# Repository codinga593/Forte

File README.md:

FORTE is a mid powered rocket with an estimated flight alitude of 137m initially, and a planned 1000m flight on a high powered motor later. 
It features a miniature onboard flight computer to verify data logging and live telemetry capabilties. 
The Flight computer has an inertial measurement unit and barometer to sense it's height and orientation. A LoRa Chip is placed onboard to stream data over 915 mHz to a ground station. 

The PCB is mainly for telemetry and datalogging, running custom firmware to achieve this. To get the PCB, you can send the gerber files to your manufacturer of choice, and buy components from online services such as LCSC, digikey or mouser. The rocket kit is available from LOC Precision and costs about $90.

This Rocket is my next step in my rocketry journey, allowing me to explore telemetry onboard rockets, efficient datalogging and building up to something more complex such as active control.

Render of Final PCB

Model of Rocket

Avionics Bay CAD

## Bill of Materials (BOM)

| Designator | Part Name | Qty | Value / Part Number | Link |
|---|---|---|---|---|
| C14, C15, C16, C17, C18, C27, C28, C29, C30, C31, C35, C36 | Capacitor | 12 | 100 nF 0603 | https://www.digikey.com/en/products/detail/murata-electronics/GRM188R71C104KA01D |
| C13, C20, C21 | Capacitor | 3 | 1 µF 0603 | https://www.digikey.com/en/products/detail/murata-electronics/GRM188R61A105KA61D |
| C24, C25 | Capacitor | 2 | 2.2 µF 0603 | https://www.digikey.com/en/products/detail/murata-electronics/GRM188R61A225KE15 |
| C22, C23 | Capacitor | 2 | 10 pF 0603 | https://www.digikey.com/en/products/detail/murata-electronics/GRM1885C1H100JA01D |
| C34 | Capacitor | 1 | 22 µF 0603 | https://www.digikey.com/en/products/detail/murata-electronics/GRM188R60J226MEA0 |
| C26, C38, C39 | Capacitor | 3 | 100 nF 0603 | https://www.digikey.com/en/products/detail/murata-electronics/GRM188R71C104KA01D |
| R2, R3, R4, R8, R9, R10, R11, R12, R13, R14, R15, R18 | Resistor | 12 | 10 kΩ 0603 | https://www.digikey.com/en/products/detail/yageo/RC0603FR-0710KL |
| R16, R17 | Resistor | 2 | 0603 220Ω | https://www.digikey.com/en/products/detail/yageo/RC0603FR |
| U3 | Microcontroller | 1 | STM32F405RGT6 | https://www.digikey.com/en/products/detail/stmicroelectronics/STM32F405RGT6 |
| IC1 | SPI Flash Memory | 1 | W25Q128JVFIQ | https://www.digikey.com/en/products/detail/winbond-electronics/W25Q128JVFIQ |
| U2 | Barometric Pressure Sensor | 1 | MS5611-01BA | https://www.digikey.com/en/products/detail/te-connectivity/MS5611-01BA |
| U4 | GNSS Receiver | 1 | u-blox MAX-M10S | https://www.digikey.com/en/products/detail/u-blox/MAX-M10S-00B |
| U5 | USB ESD Protection | 1 | USBLC6-2SC6 | https://www.digikey.com/en/products/detail/stmicroelectronics/USBLC6-2SC6 |
| U13 | Buck Converter | 1 | TPS54525PWPR | https://www.digikey.com/en/products/detail/texas-instruments/TPS54525PWPR |
| Y2 | Crystal | 1 | 16 MHz SMD | https://www.digikey.com/en/products/detail/ecs-inc/ECS-160-20-33Q |
| J2 | RF Connector | 1 | U.FL-R-SMT-01 | https://www.digikey.com/en/products/detail/hirose-electric/U-FL-R-SMT-01 |
| J4 | USB-C Connector | 1 | USB4105-GF-A | https://www.digikey.com/en/products/detail/gct/USB4105-GF-A |
| TP1, TP2 | Test Point | 2 | PCB Test Pad | https://www.digikey.com/en/products/detail/keystone-electronics/5015 |
| SW2 | Slide Switch | 1 | SPDT (PCM12 style) | https://www.digikey.com/en/products/detail/c-k/PCM12SMTR |

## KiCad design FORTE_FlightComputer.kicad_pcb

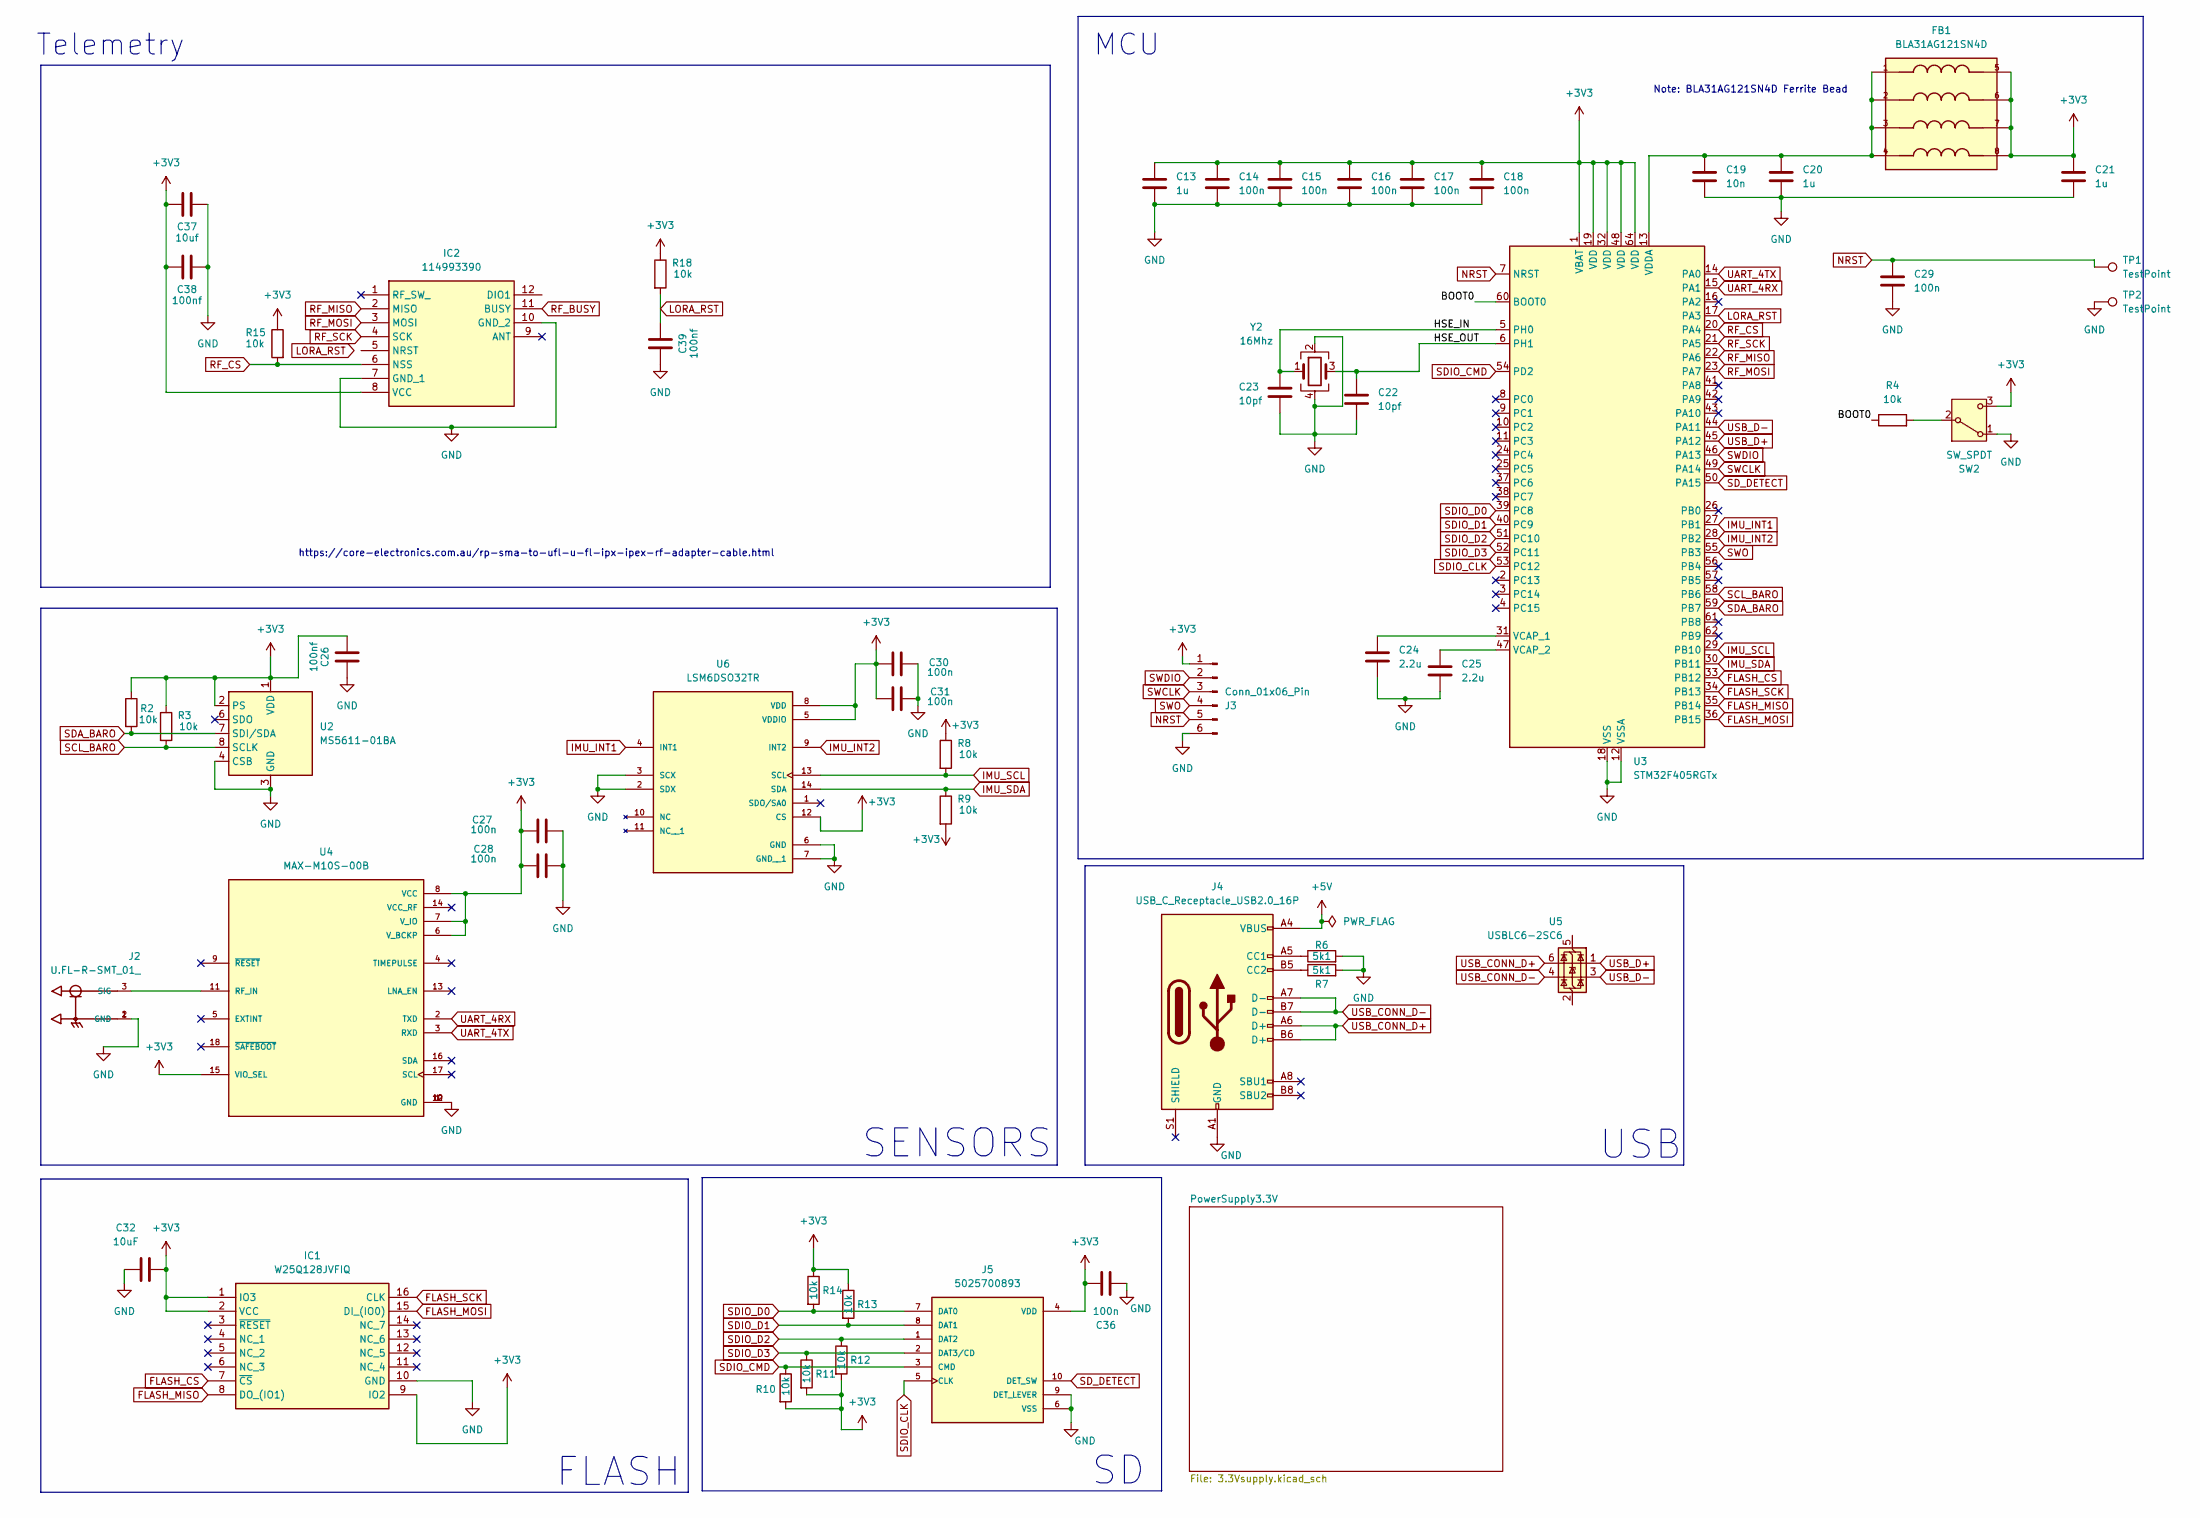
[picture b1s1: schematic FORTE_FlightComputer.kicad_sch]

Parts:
C13, C20, C21: 1u; C_0603_1608Metric
C14, C15, C16, C17, C18, C27, C28, C29, C30, C31, C36: 100n; C_0603_1608Metric
C19: 10n; C_0603_1608Metric
C22, C23: 10pf; C_0603_1608Metric
C24, C25: 2.2u; C_0603_1608Metric
C26, C38, C39: 100nf; C_0603_1608Metric
C32: 10uF; C_0603_1608Metric
C37: 10uf; C_0603_1608Metric
FB1: BLA31AG121SN4D; FB_BLA31AG121SN4D; PARTREV JENF243A–0008N-01
IC1: W25Q128JVFIQ; SOIC127P1032X264-16N; Mouser Part Number 454-W25Q128JVFIQ
IC2: 114993390; Mouser Part Number 713-114993390
J2: U.FL-R-SMT_01_; HRS_U.FL-R-SMT_01_
J3: Conn_01x06_Pin; PinHeader_1x06_P2.54mm_Vertical
J4: USB_C_Receptacle_USB2.0_16P; USB_C_Receptacle_GCT_USB4105-xx-A_16P_TopMnt_Horizontal
J5: 5025700893; MOLEX_5025700893
R2, R3, R4, R8, R9, R10, R11, R12, R13, R14, R15, R18: 10k; R_0603_1608Metric
R6, R7: 5k1; R_0603_1608Metric
SW2: SW_SPDT; SW_SPDT_PCM12
TP1, TP2: TestPoint; TestPoint_Pad_1.5x1.5mm
U2: MS5611-01BA; LGA-8_3x5mm_P1.25mm
U3: STM32F405RGTx; LQFP-64_10x10mm_P0.5mm
U4: MAX-M10S-00B; XCVR_MAX-M10S-00B; PARTREV C1
U5: USBLC6-2SC6; SOT-23-6
U6: LSM6DSO32TR; XDCR_LSM6DSO32TR; PARTREV 1
Y2: 16Mhz; Crystal_SMD_3225-4Pin_3.2x2.5mm

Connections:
+3V3: C13.1, C14.1, C15.1, C16.1, C17.1, C18.1, C21.1, C26.1, C27.1, C28.1, C30.1, C31.1, C32.2, C36.2, C37.1, C38.1, FB1.5, FB1.6, FB1.7, FB1.8, IC1.1 (IO3), IC1.2 (VCC), IC1.9 (IO2), IC2.8 (VCC), J3.1, J5.4 (VDD), R2.1, R3.1, R8.1, R9.2, R10.2, R11.2, R12.2, R13.1, R14.1, R15.1, R18.1, SW2.3 (C), U2.1 (VDD), U2.2 (PS), U3.1 (VBAT), U3.19 (VDD), U3.32 (VDD), U3.48 (VDD), U3.64 (VDD), U4.6 (V_BCKP), U4.7 (V_IO), U4.8 (VCC), U4.15 (VIO_SEL), U6.5 (VDDIO), U6.8 (VDD), U6.12 (CS); also elsewhere on the board
+5V: J4.A4 (VBUS), J4.A9 (VBUS), J4.B4 (VBUS), J4.B9 (VBUS)
/BOOT0: R4.1, U3.60 (BOOT0)
/HSE_IN: C23.1, U3.5 (PH0), Y2.1
/HSE_OUT: C22.1, U3.6 (PH1), Y2.3
FLASH_CS: IC1.7 (~CS), U3.33 (PB12)
FLASH_MISO: IC1.8 (DO_(IO1)), U3.35 (PB14)
FLASH_MOSI: IC1.15 (DI_(IO0)), U3.36 (PB15)
FLASH_SCK: IC1.16 (CLK), U3.34 (PB13)
GND: C13.2, C14.2, C15.2, C16.2, C17.2, C18.2, C19.2, C20.2, C21.2, C22.2, C23.2, C24.2, C25.2, C26.2, C27.2, C28.2, C29.2, C30.2, C31.2, C32.1, C36.1, C37.2, C38.2, C39.1, IC1.10 (GND), IC2.7 (GND_1), IC2.10 (GND_2), J2.1 (GND), J2.2 (GND), J3.6, J4.A1 (GND), J4.A12 (GND), J4.B1 (GND), J4.B12 (GND), J5.6 (VSS), J5.9 (DET_LEVER), R6.2, R7.2, SW2.1 (A), TP2.1, U2.3 (GND), U2.4 (CSB), U2.5 (CSB), U3.12 (VSSA), U3.18 (VSS), U3.63 (VSS), U4.1 (GND), U4.10 (GND), U4.12 (GND), U6.2 (SDX), U6.3 (SCX), U6.6 (GND), U6.7 (GND__1), Y2.2, Y2.4; also elsewhere on the board
IMU_INT1: U3.27 (PB1), U6.4 (INT1)
IMU_INT2: U3.28 (PB2), U6.9 (INT2)
IMU_SCL: R8.2, U3.29 (PB10), U6.13 (SCL)
IMU_SDA: R9.1, U3.30 (PB11), U6.14 (SDA)
LORA_RST: C39.2, R18.2, U3.17 (PA3)
NRST: C29.1, J3.5, TP1.1, U3.7 (NRST)
unnamed: J2.3 (SIG), U4.11 (RF_IN)
unnamed: J4.A5 (CC1), R6.1
unnamed: J4.B5 (CC2), R7.1
unnamed: R4.2, SW2.2 (B)
unnamed: C24.1, U3.31 (VCAP_1)
unnamed: C25.1, U3.47 (VCAP_2)
unnamed: C19.1, C20.1, FB1.1, FB1.2, FB1.3, FB1.4, U3.13 (VDDA)
RF_BUSY: IC2.11 (BUSY)
RF_CS: IC2.6 (NSS), R15.2, U3.20 (PA4)
RF_MISO: IC2.2 (MISO), U3.22 (PA6)
RF_MOSI: IC2.3 (MOSI), U3.23 (PA7)
RF_SCK: IC2.4 (SCK), U3.21 (PA5)
SCL_BARO: R3.2, U2.8 (SCLK), U3.58 (PB6)
SDA_BARO: R2.2, U2.7 (SDI/SDA), U3.59 (PB7)
SDIO_CLK: J5.5 (CLK), U3.53 (PC12)
SDIO_CMD: J5.3 (CMD), R10.1, U3.54 (PD2)
SDIO_D0: J5.7 (DAT0), R14.2, U3.39 (PC8)
SDIO_D1: J5.8 (DAT1), R13.2, U3.40 (PC9)
SDIO_D2: J5.1 (DAT2), R12.1, U3.51 (PC10)
SDIO_D3: J5.2 (DAT3/CD), R11.1, U3.52 (PC11)
SD_DETECT: J5.10 (DET_SW), U3.50 (PA15)
SWCLK: J3.3, U3.49 (PA14)
SWDIO: J3.2, U3.46 (PA13)
SWO: J3.4, U3.55 (PB3)
UART_4RX: U3.15 (PA1), U4.2 (TXD)
UART_4TX: U3.14 (PA0), U4.3 (RXD)
USB_CONN_D+: J4.A6 (D+), J4.B6 (D+), U5.6 (I/O1)
USB_CONN_D-: J4.A7 (D-), J4.B7 (D-), U5.4 (I/O2)
USB_D+: U3.45 (PA12), U5.1 (I/O1)
USB_D-: U3.44 (PA11), U5.3 (I/O2)

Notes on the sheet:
Note: BLA31AG121SN4D Ferrite Bead
FLASH
SENSORS
USB
MCU
https://core-electronics.com.au/rp-sma-to-ufl-u-fl-ipx-ipex-rf-adapter-cable.html
Telemetry

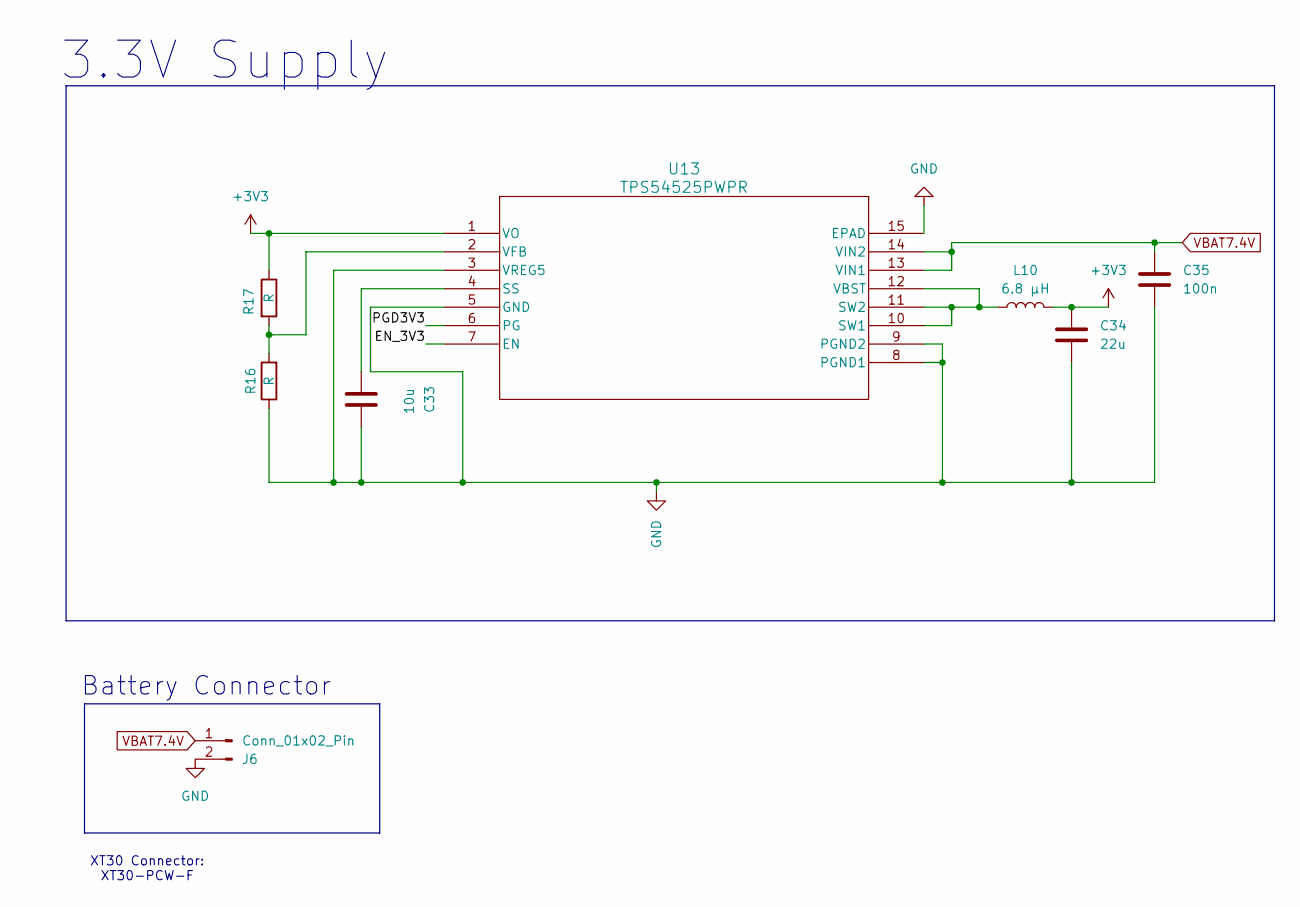
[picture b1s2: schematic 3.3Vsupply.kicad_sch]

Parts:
C33: 10u; C_0603_1608Metric
C34: 22u; C_0603_1608Metric
C35: 100n; C_0603_1608Metric
J6: Conn_01x02_Pin; AMASS_XT30PW-F_1x02_P2.50mm_Horizontal
L10: 6.8 µH; WE-XHMA_6060
R16, R17: R; R_0603_1608Metric
U13: TPS54525PWPR; PWP14_2P31X2P46_TEX

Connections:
+3V3: C34.1, L10.2, R17.1, U13.1 (VO); also elsewhere on the board
/PowerSupply3.3V/EN_3V3: U13.7 (EN)
/PowerSupply3.3V/PGD3V3: U13.6 (PG)
GND: C33.1, C34.2, C35.2, J6.2, R16.1, U13.3 (VREG5), U13.5 (GND), U13.8 (PGND1), U13.9 (PGND2), U13.15 (EPAD); also elsewhere on the board
unnamed: C33.2, U13.4 (SS)
unnamed: L10.1, U13.10 (SW1), U13.11 (SW2), U13.12 (VBST)
unnamed: R16.2, R17.2, U13.2 (VFB)
VBAT7.4V: C35.1, J6.1, U13.13 (VIN1), U13.14 (VIN2)

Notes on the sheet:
XT30 Connector: XT30-PCW-F
3.3V Supply
Battery Connector

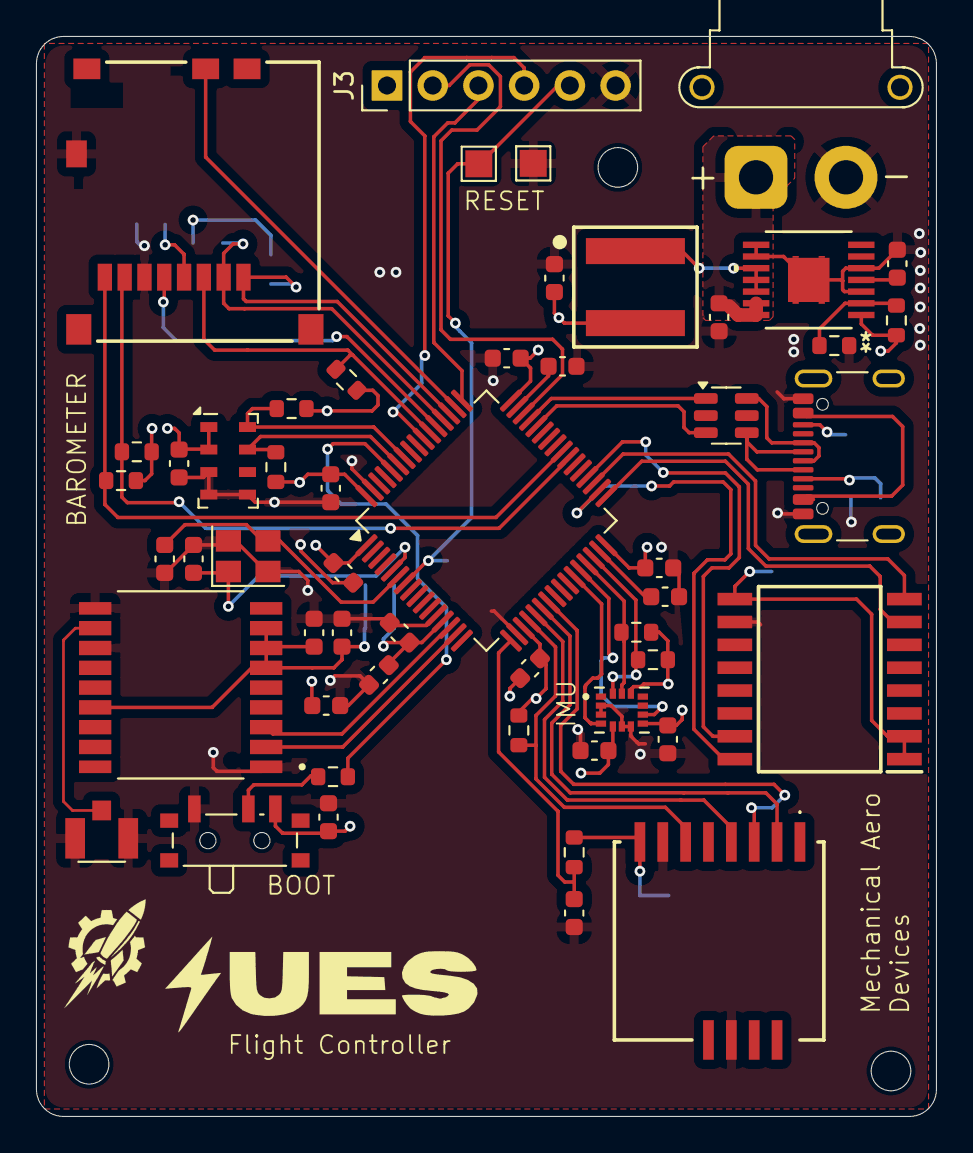
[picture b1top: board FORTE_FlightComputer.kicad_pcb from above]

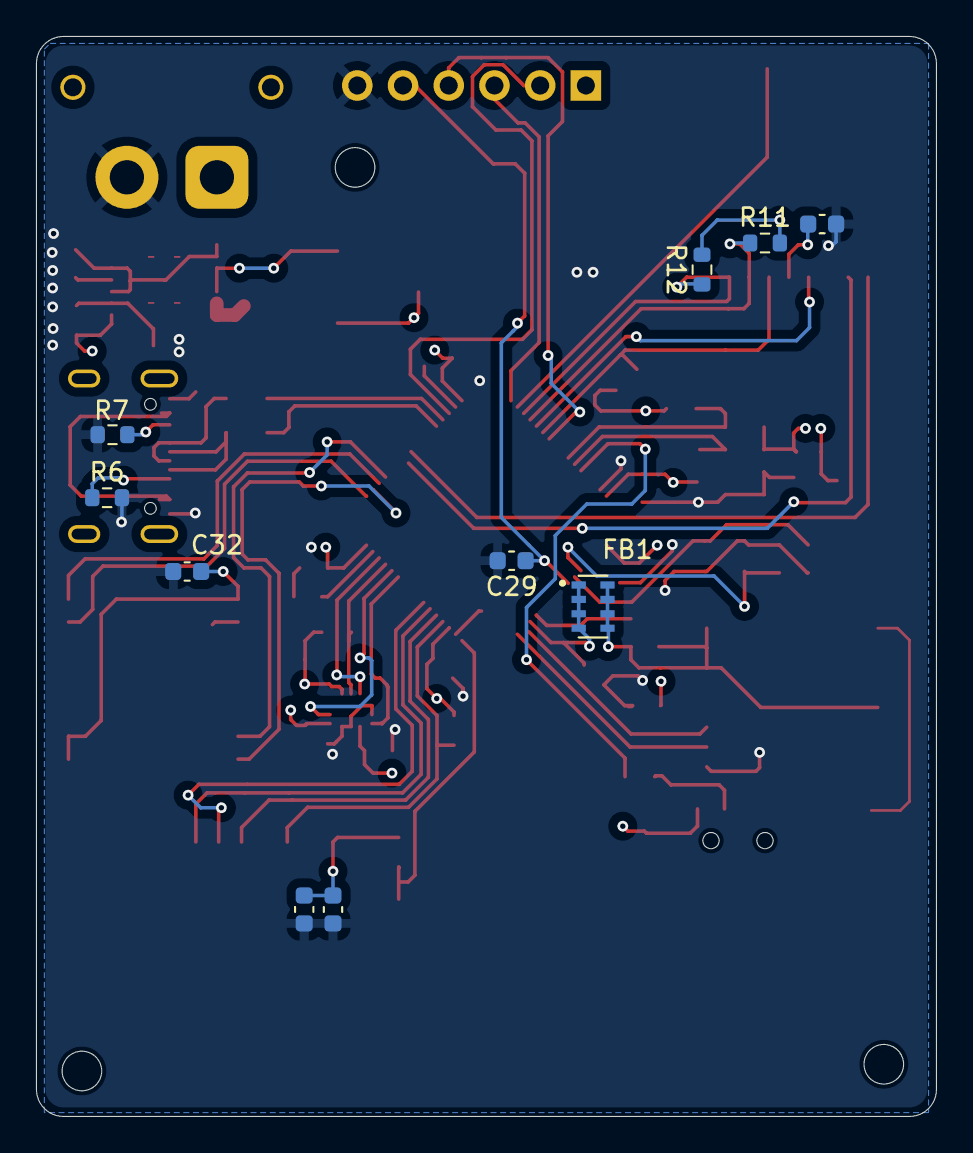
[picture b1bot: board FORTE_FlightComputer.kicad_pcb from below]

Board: 4 copper layers, 50.0 x 60.0 mm, 62 parts (10 on the bottom side), 49 nets.

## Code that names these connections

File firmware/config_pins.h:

#pragma once

#include <Arduino.h>
#include <SPI.h>
#include <Wire.h>

// ===== Bus assignment =====
// STM32F405 typically exposes Wire (I2C1) and Wire1 (I2C2) in STM32Duino.
#if defined(WIRE_INTERFACES_COUNT) && (WIRE_INTERFACES_COUNT > 1)
#define IMU_I2C_BUS Wire1
#else
#define IMU_I2C_BUS Wire
#endif

#define BARO_I2C_BUS Wire

// GPS on UART4 RX path (module TX -> MCU RX). In STM32Duino, Serial4 maps to UART4.
#define GPS_UART Serial4

// SPI buses (adjust if your board variant names differ).
#define FLASH_SPI_BUS SPI
#define LORA_SPI_BUS SPI

// ===== Addresses =====
static constexpr uint8_t IMU_I2C_ADDR = 0x6A;
static constexpr uint8_t MS5611_I2C_ADDR = 0x77;

// ===== W25Q128 pins =====
// Replace these with your PCB net mapping.
static constexpr uint8_t FLASH_CS_PIN = PB0;

// ===== SX1262 pins =====
// Replace these with your PCB net mapping.
static constexpr uint8_t LORA_NSS_PIN = PB12;
static constexpr uint8_t LORA_BUSY_PIN = PB1;
static constexpr uint8_t LORA_DIO1_PIN = PB2;
static constexpr uint8_t LORA_RESET_PIN = PB10;

// ===== Runtime timing =====
static constexpr uint32_t DEBUG_BAUD = 115200;
static constexpr uint32_t GPS_BAUD = 9600;
static constexpr uint32_t LOOP_PERIOD_MS = 20;       // 50Hz sample loop
static constexpr uint32_t LORA_TX_INTERVAL_MS = 200; // 5Hz telemetry
static constexpr uint32_t MIN_FLIGHT_TIME_MS = 6000;
static constexpr float LORA_FREQ_MHZ = 915.0f;       // US915 default

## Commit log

2026-03-02 Add files via upload
    This is the final open rocket file for FORTE, with a mass component to simulate the avionics bay in the payload section.
2026-03-07 Create s
